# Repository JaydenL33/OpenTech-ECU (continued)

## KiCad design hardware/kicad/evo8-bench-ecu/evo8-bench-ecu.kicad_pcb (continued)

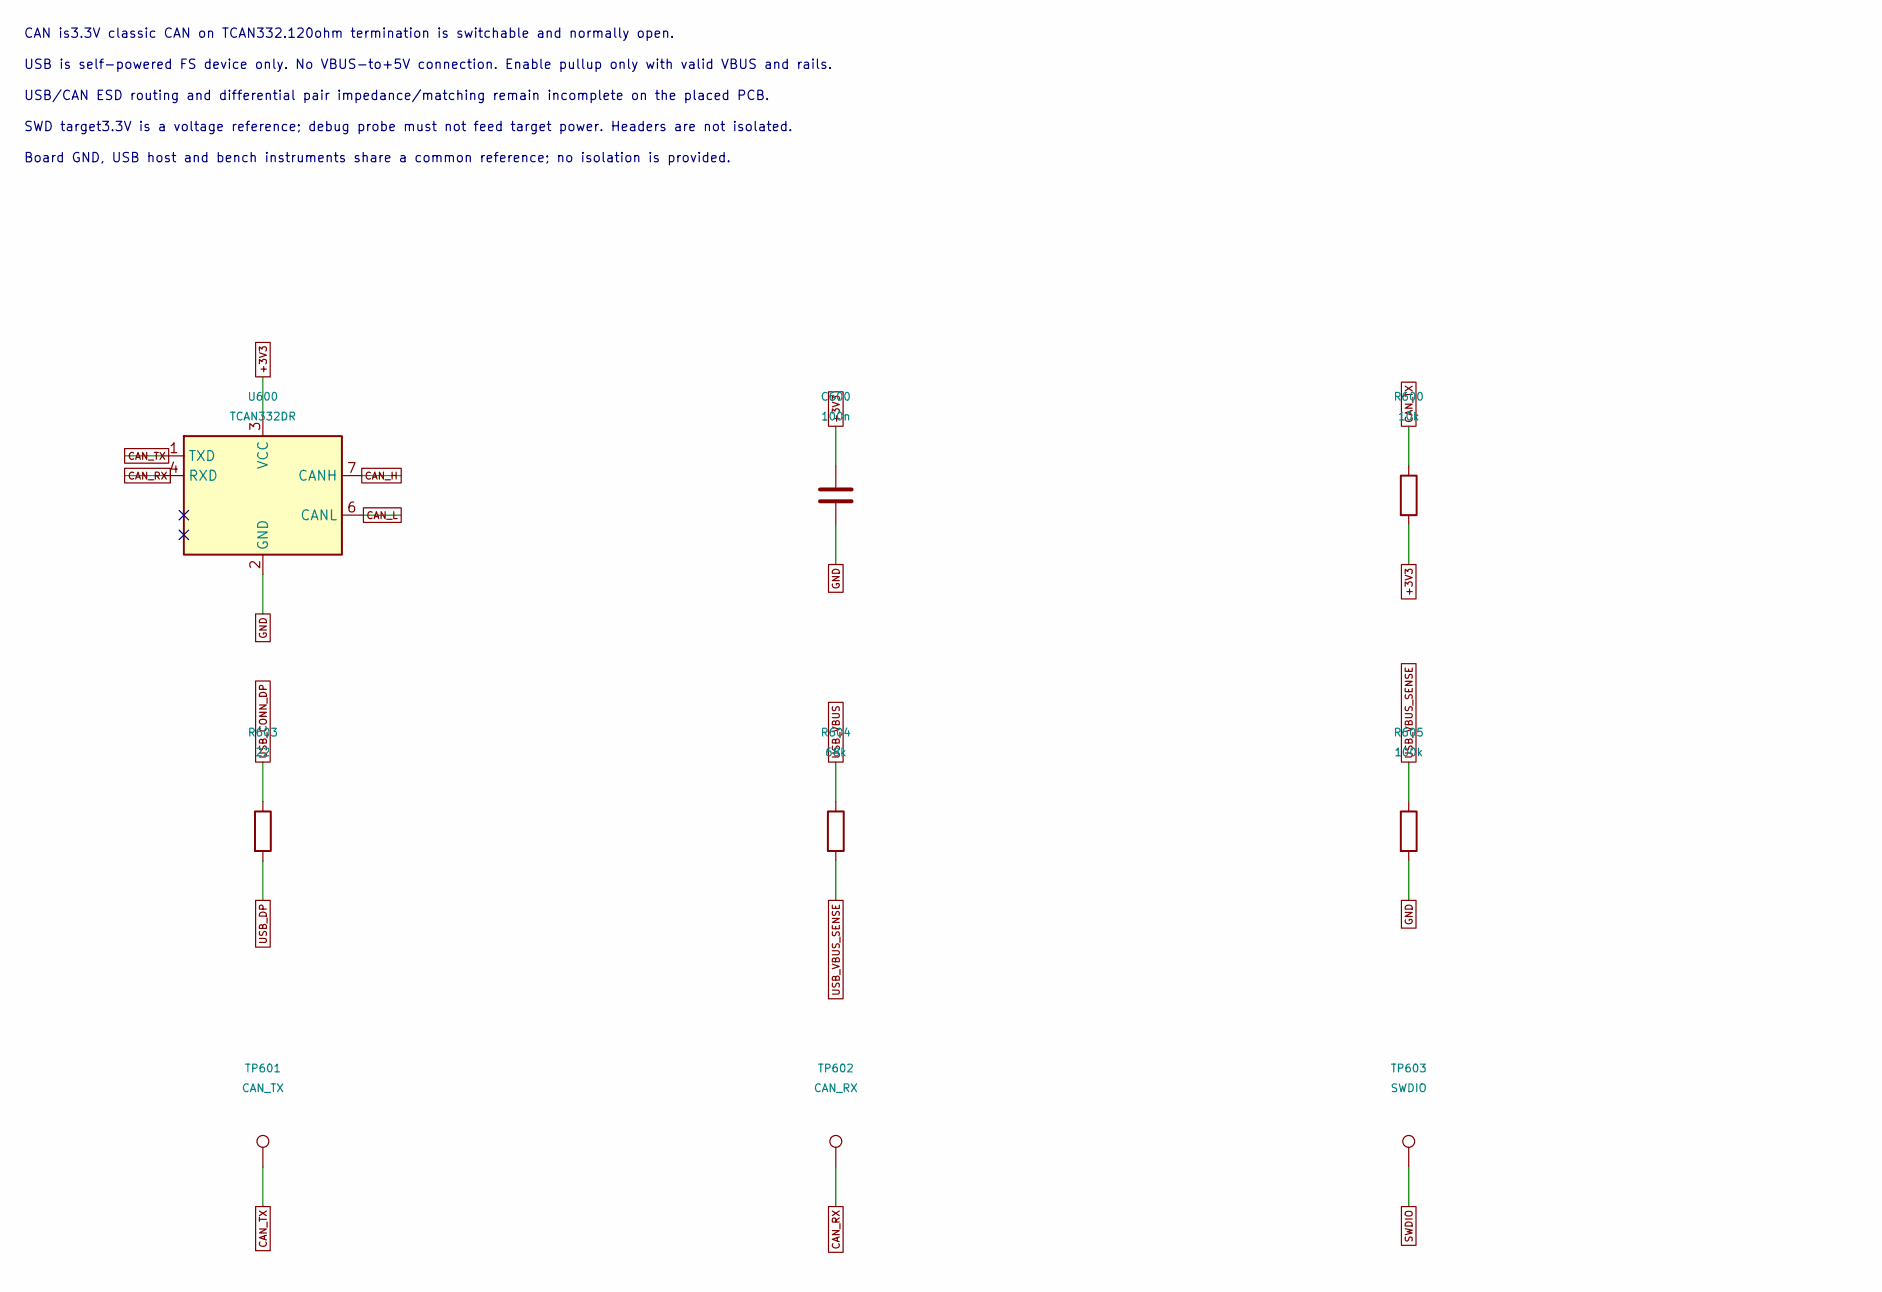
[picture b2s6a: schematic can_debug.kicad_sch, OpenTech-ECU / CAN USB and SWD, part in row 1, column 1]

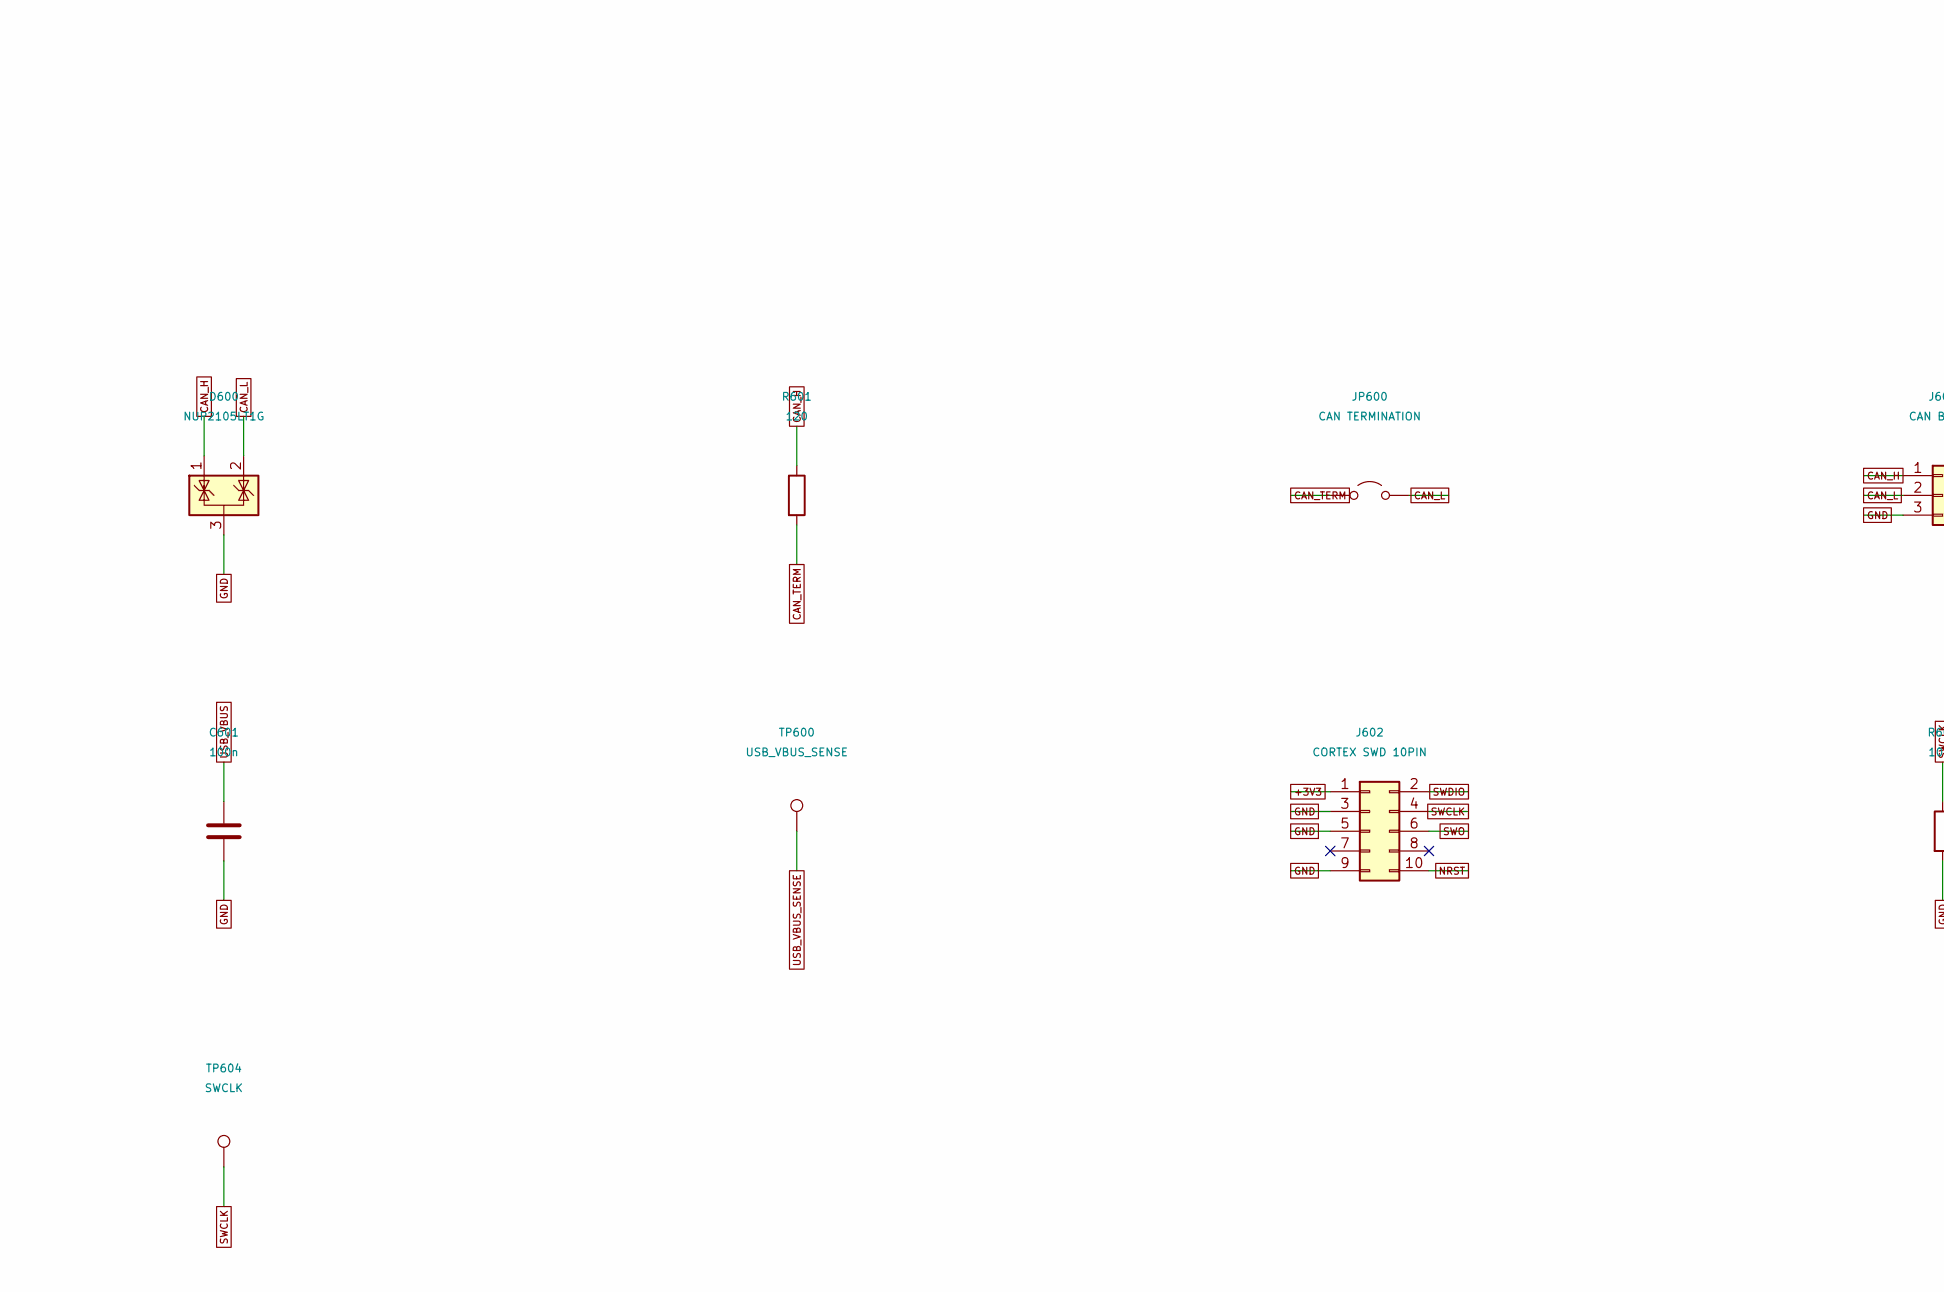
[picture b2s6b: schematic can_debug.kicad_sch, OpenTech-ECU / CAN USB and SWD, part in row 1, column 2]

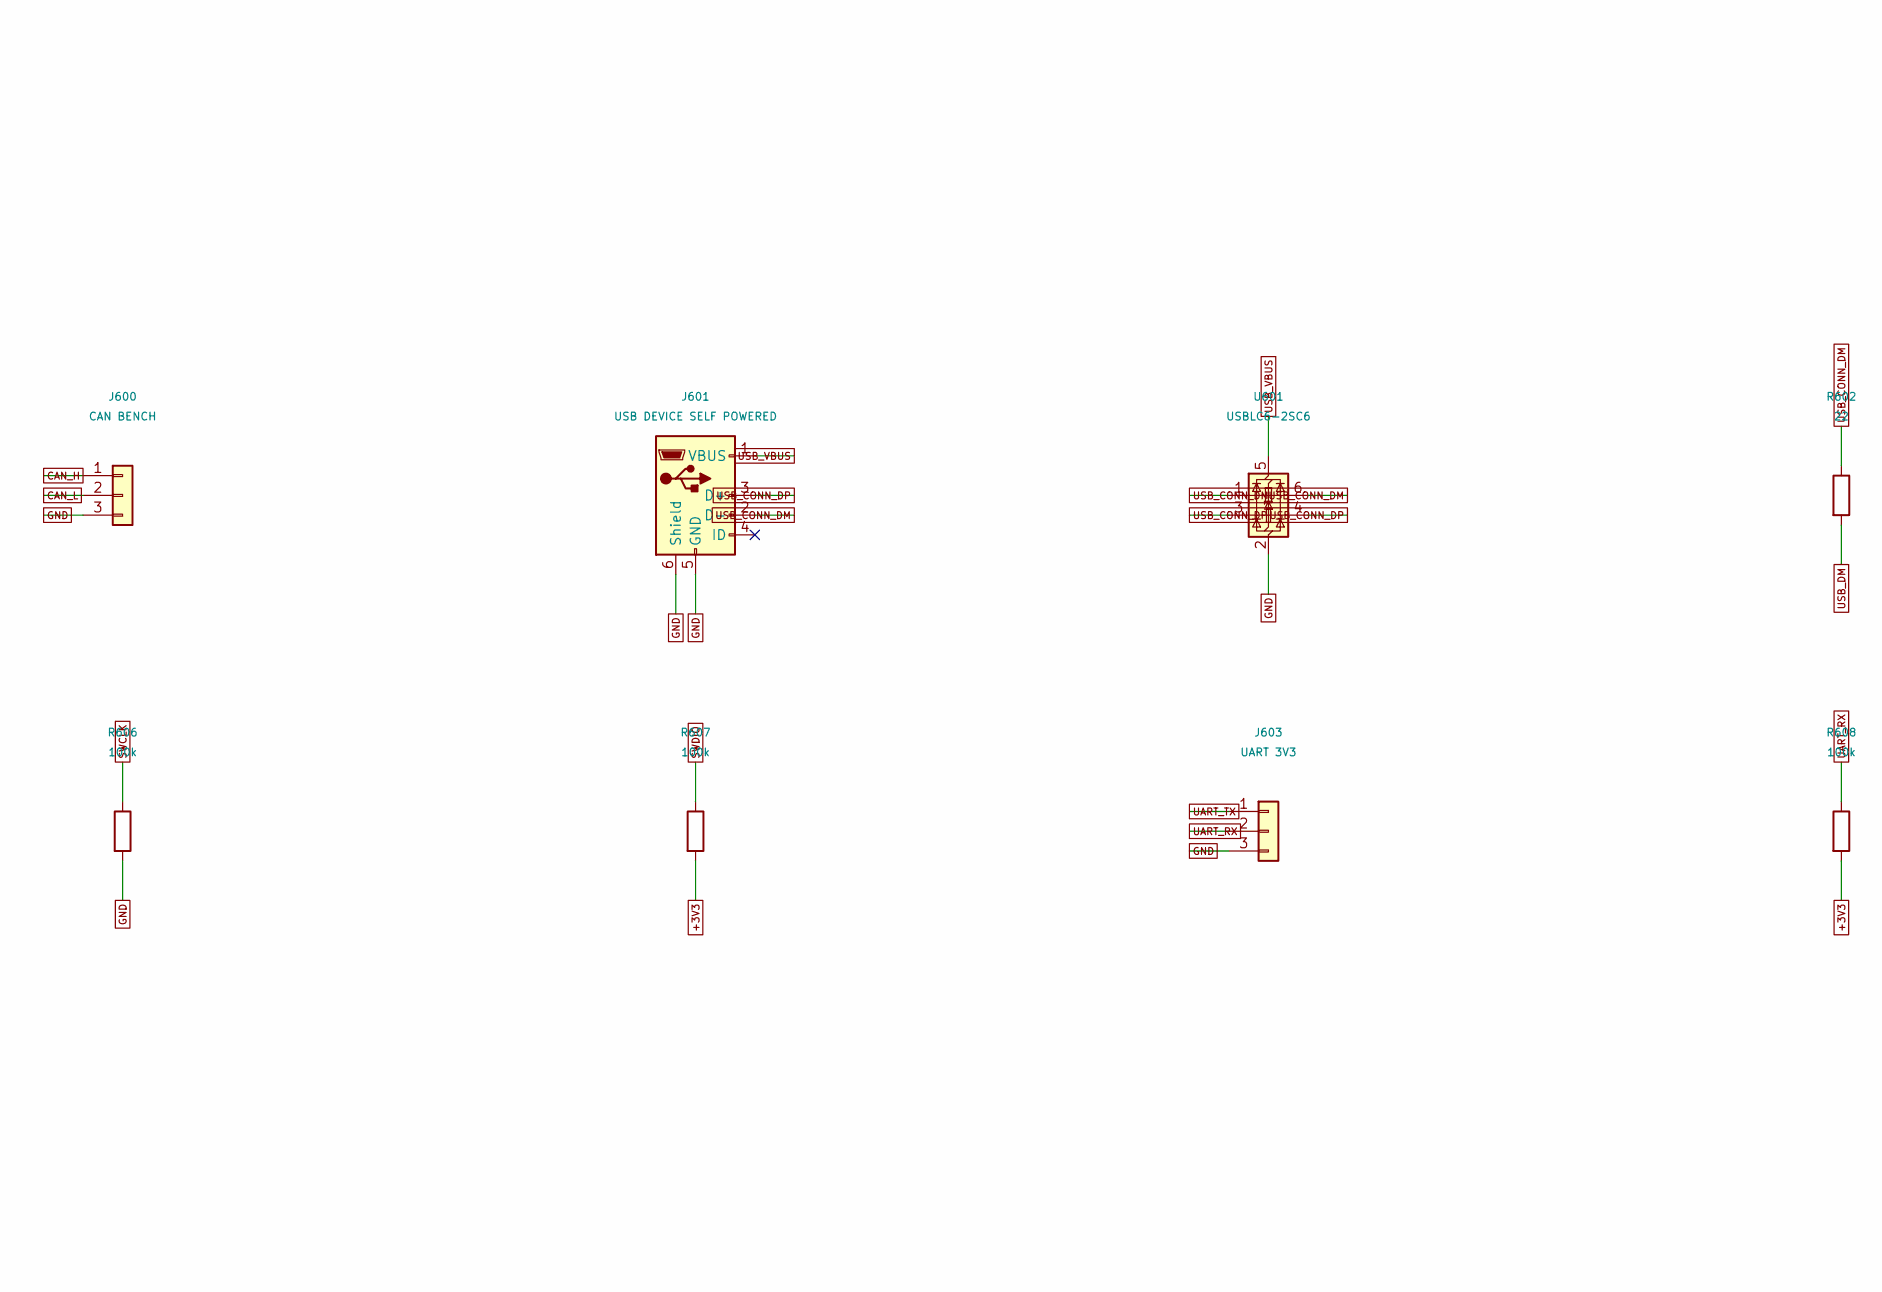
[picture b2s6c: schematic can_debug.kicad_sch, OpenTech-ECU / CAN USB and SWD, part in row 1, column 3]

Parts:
C600, C601: 100n; C_0805_2012Metric; MPN GRM21BR71H104KA01L
D600: NUP2105LT1G; SOT-23; MPN NUP2105LT1G
J600: CAN BENCH; TerminalBlock_Phoenix_MKDS-1,5-3-5.08_1x03_P5.08mm_Horizont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; MPN 1715734
J601: USB DEVICE SELF POWERED; USB_Micro-B_Amphenol_10118194-0001LF_Horizontal; MPN 10118194-0001LF
J602: CORTEX SWD 10PIN; PinHeader_2x05_P1.27mm_Vertical; MPN 20021121-00010T4LF
J603: UART 3V3; TerminalBlock_Phoenix_MKDS-1,5-3-5.08_1x03_P5.08mm_Horizont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; MPN 1715734
JP600: CAN TERMINATION; PinHeader_1x02_P2.54mm_Vertical; MPN 61300211121
R600: 10k; R_0805_2012Metric; MPN RC0805FR-0710KL
R601: 120; R_0805_2012Metric; MPN RC0805FR-07120RL
R602, R603: 22; R_0805_2012Metric; MPN RC0805FR-0722RL
R604: 68k; R_0805_2012Metric; MPN RC0805FR-0768KL
R605, R606, R607, R608: 100k; R_0805_2012Metric; MPN RC0805FR-07100KL
TP600: USB_VBUS_SENSE; TestPoint_THTPad_D2.0mm_Drill1.0mm; MPN 5010
TP601: CAN_TX; TestPoint_THTPad_D2.0mm_Drill1.0mm; MPN 5010
TP602: CAN_RX; TestPoint_THTPad_D2.0mm_Drill1.0mm; MPN 5010
TP603: SWDIO; TestPoint_THTPad_D2.0mm_Drill1.0mm; MPN 5010
TP604: SWCLK; TestPoint_THTPad_D2.0mm_Drill1.0mm; MPN 5010
U600: TCAN332DR; SOIC-8_3.9x4.9mm_P1.27mm; MPN TCAN332DR
U601: USBLC6-2SC6; SOT-23-6; MPN USBLC6-2SC6

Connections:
+3V3: C600.1, J602.1, R600.2, R607.2, R608.2, U600.3 (VCC); also elsewhere on the board
CAN_H: D600.1 (K), J600.1, R601.1, U600.7 (CANH)
CAN_L: D600.2 (K), J600.2, JP600.2 (B), U600.6 (CANL)
CAN_RX: TP602.1, U600.4 (RXD); also elsewhere on the board
CAN_TERM: JP600.1 (A), R601.2
CAN_TX: R600.1, TP601.1, U600.1 (TXD); also elsewhere on the board
GND: C600.2, C601.2, D600.3 (A), J600.3, J601.5 (GND), J601.6 (Shield), J602.3, J602.5, J602.9, J603.3, R605.2, R606.2, U600.2 (GND), U601.2 (GND); also elsewhere on the board
NRST: J602.10; also elsewhere on the board
SWCLK: J602.4, R606.1, TP604.1; also elsewhere on the board
SWDIO: J602.2, R607.1, TP603.1; also elsewhere on the board
SWO: J602.6; also elsewhere on the board
UART_RX: J603.2, R608.1; also elsewhere on the board
UART_TX: J603.1; also elsewhere on the board
USB_CONN_DM: J601.2 (D-), R602.1, U601.1 (I/O1), U601.6 (I/O1)
USB_CONN_DP: J601.3 (D+), R603.1, U601.3 (I/O2), U601.4 (I/O2)
USB_DM: R602.2; also elsewhere on the board
USB_DP: R603.2; also elsewhere on the board
USB_VBUS: C601.1, J601.1 (VBUS), R604.1, U601.5 (VBUS)
USB_VBUS_SENSE: R604.2, R605.1, TP600.1; also elsewhere on the board

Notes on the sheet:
CAN is3.3V classic CAN on TCAN332.120ohm termination is switchable and normally open.
USB is self-powered FS device only. No VBUS-to+5V connection. Enable pullup only with valid VBUS and rails.
USB/CAN ESD routing and differential pair impedance/matching remain incomplete on the placed PCB.
SWD target3.3V is a voltage reference; debug probe must not feed target power. Headers are not isolated.
Board GND, USB host and bench instruments share a common reference; no isolation is provided.
